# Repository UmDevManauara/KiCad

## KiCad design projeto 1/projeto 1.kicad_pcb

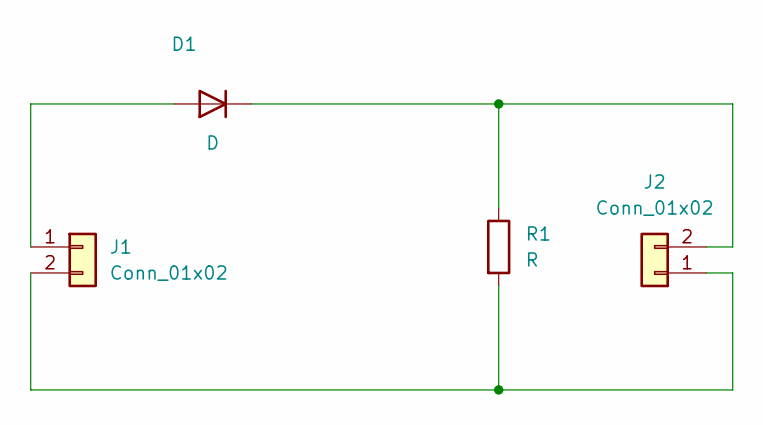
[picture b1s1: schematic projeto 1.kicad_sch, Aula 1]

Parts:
D1: D; D_DO-41_SOD81_P7.62mm_Horizontal
J1, J2: Conn_01x02; PinHeader_1x02_P2.00mm_Vertical
R1: R; R_Axial_DIN0207_L6.3mm_D2.5mm_P10.16mm_Horizontal

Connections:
unnamed: D1.2 (A), J1.1
unnamed: D1.1 (K), J2.2, R1.1
unnamed: J1.2, J2.1, R1.2

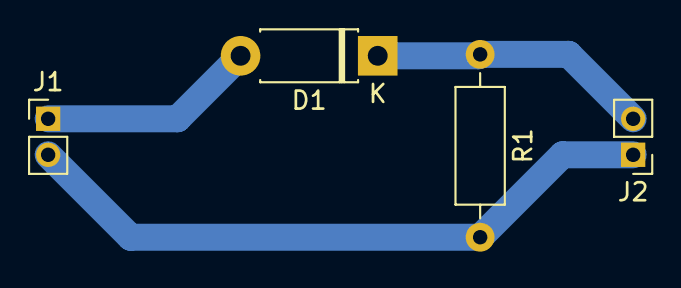
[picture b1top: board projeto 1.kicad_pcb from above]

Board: 2 copper layers, 4 parts (0 on the bottom side), 3 nets.

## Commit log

2024-05-20 kicad
